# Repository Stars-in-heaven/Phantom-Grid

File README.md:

# PHANTOM GRID

> *Offline-first. Air-gapped. Encrypted. Built for the field.*

Phantom Grid is a series of purpose-built handheld devices engineered for those who operate outside the comfort of connectivity. No Wi-Fi. No cloud sync. No IP assignment. Every hardware and firmware decision is governed by a single principle: **security first, convenience never.**

https://phantom-grid.netlify.app - our site :0 **( has some issues/WIP cuz I keep running out of Netlify credit )**

---

## Series

| ID | Name | Description |
|----|------|-------------|
| **S** | Survival | Bare minimum. Maximum efficiency. Built to run when nothing else does. |
| **T** | Tactical | Feature-packed, encrypted, hardened. Heavy-duty field use. |
| **X** | Experimental | Highly specialised. Each unit unique. Not for general deployment. |
| **C** | Cyber | Fully off-grid. Offensive posture. Maximum resource load. |

---

## Current Build — T-V.1

The first Tactical series device. Dual-panel, hinged form factor with three independent displays, local sensor data, GPS, and an air-gapped file archive terminal.

### Architecture

- **Dual ESP32-C6 SuperMini** — one per side, connected via 4-wire UART hinge link
- **Left side** — Tactical Overwatch Panel (OLEDs, 5-way nav, GPS, moisture, battery)
- **Right side** — Archive Command Terminal (ILI9341 TFT, microSD, tactile buttons)
- **Power** — LiPo 2000–2500mAh → TP4056 (dual protection) → 3.3V buck converter → shared rail via hinge

### Displays

| Display | Role | Interface |
|---------|------|-----------|
| 0.91" OLED 128×32 | Battery, time, date | I²C |
| 1.5" OLED 128×128 | GPS, moisture, sensor data | I²C via TCA9548A |
| 2.4" TFT ILI9341 | File browser, archive terminal | SPI |

### Storage

Files are loaded onto the microSD card by **physically removing it**, writing via USB adapter on a separate machine, and reinserting. No cloud sync. No Wi-Fi. No detectable radio signature. By design.

---

## Build Phases

- [x] **Phase 1** — Architecture & Pinout
- [x] **Phase 2** — Breadboard Prototype
- [ ] **Phase 3** — Firmware Foundation
- [x] **Phase 4** — Feature Layer
- [ ] **Phase 5** — Firmware Hardening
- [ ] **Phase 6** — Physical Build

 (working on getting the components to build the first
  prototype to begin firmware)

---

## Firmware Protection (Phase 5)

- Strip all debug symbols, aggressive optimisation (`-O2/-O3`)
- Obfuscator-LLVM control flow mangling
- CRC/hash self-check on boot — halts if tampered
- Chip ID binding — binds to first chip it runs on, cloning breaks it
- Sensitive logic derived at runtime, never stored plainly in binary
- Binary-only distribution with checksum and signature

---

## Repository Structure

```
phantom-grid/
├── Enclosure/               # Case 3d model
│   ├── Enclosure.f3d
│   ├── Enclosure.step
│   └── Enclosure.stl
|
├── PCBs/               # Kicad PCB files
│   ├── left side/
|   |    ├── left_side.kicad_pcb
|   |    ├── left_side.kicad_pro
|   |    └── left_side.kicad_sch
|   |
│   └── right side/
|       ├── right.kicad_pcb
|       ├── right.kicad_pro
|       └── right.kicad_sch
|  
├── .gitignore
├── README.md    
└── LICENSE

```

---

## Estimated Build Cost

**~£43–80** depending on component sourcing. All parts sourced from AliExpress. Full BOM available in `site/bom.html`.

---

## Progress --  T-V.1

### Left side ( Tactical over-watch Panel )
| Schematic        | PCB           | 3d-view  |
| ------------- |:-------------:| -----:|
|               |  |         |

### Right side ( Archive Terminal Panel )
| Schematic        | PCB           | 3d-view  |
| ------------- |:-------------:| -----:|
|  |  |  |

### ENCLOSURE:
 (It is split in half, but due to this being a prototype it has no screw holes, As I plan to drill them in for testing sizes and such. And then in more final models it will advance to having screw holes.)

---

## Licensing

This project uses a dual licensing model:

| What | Licence | Details |
|------|---------|---------|
| PCB files, enclosure, skeleton firmware | **CERN-OHL-S v2** | Open hardware — modifications must be released under the same licence |
| Full feature firmware | **Proprietary** | Never released — binary only, chip-bound, encrypted |

The open skeleton gives you everything you need to understand how the device is wired and structured. The full firmware with all features ships only with commercially built units and is protected by hardware-level encryption and chip binding. You are free to build your own version using the open source materials — you cannot take the commercial firmware.

---

*PG-T-V.1 / REV.002 / ENCRYPTED / AIR-GAPPED*

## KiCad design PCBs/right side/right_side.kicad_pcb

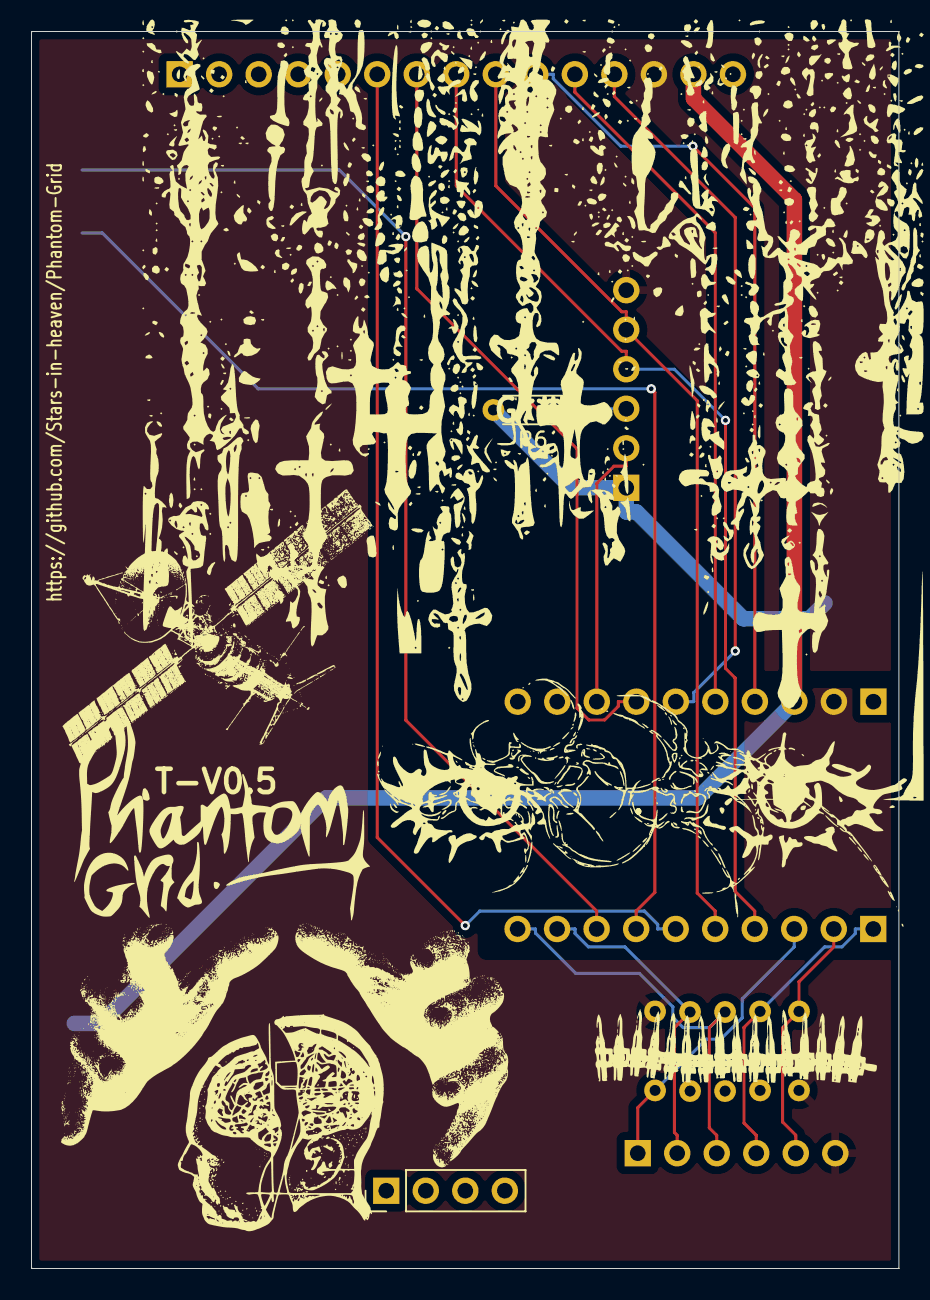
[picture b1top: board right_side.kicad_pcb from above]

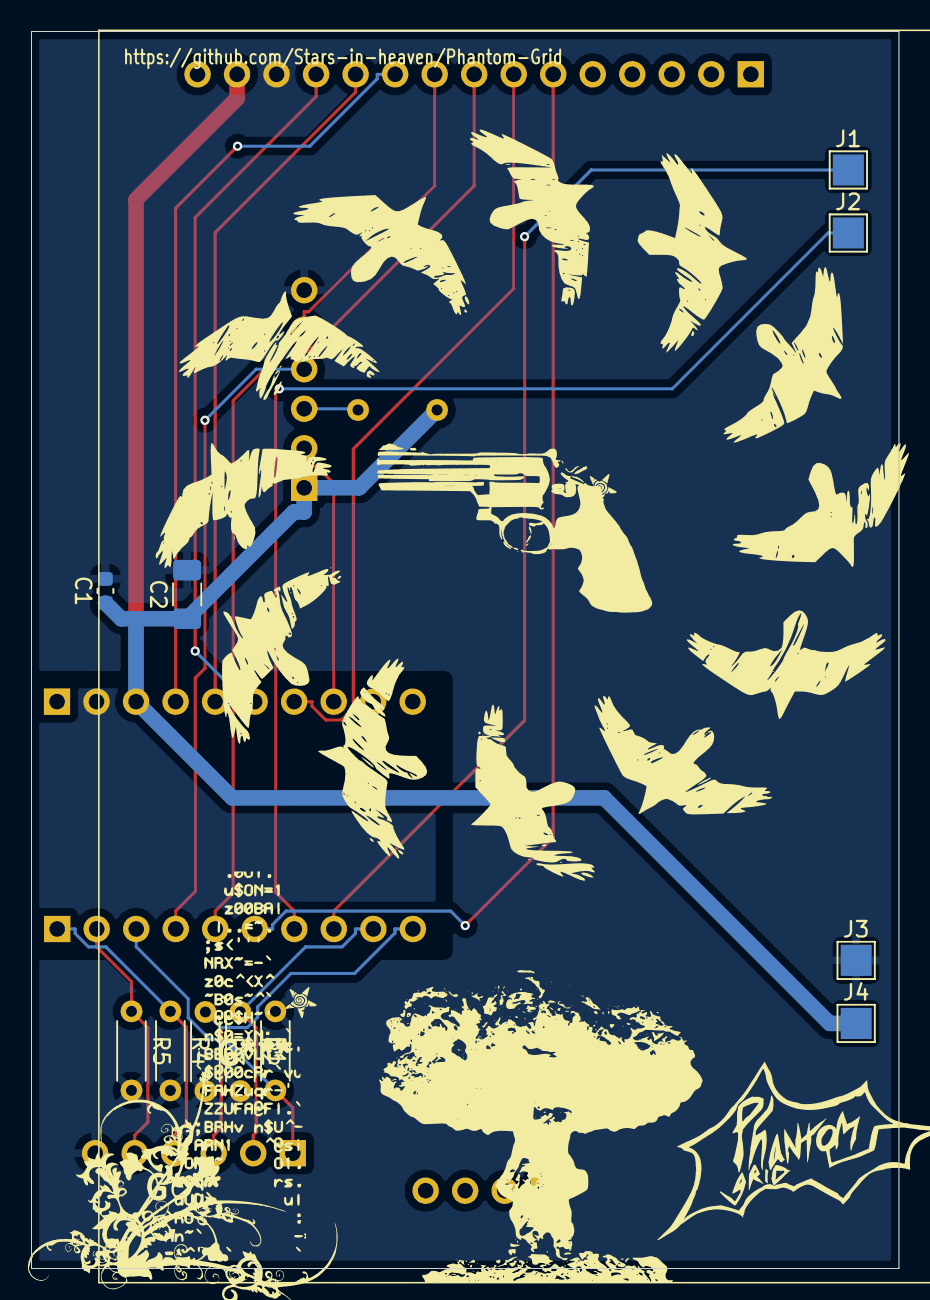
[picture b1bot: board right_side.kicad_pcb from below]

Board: 2 copper layers, 55.8 x 79.5 mm, 18 parts (13 on the bottom side), 18 nets.

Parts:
5-way_nav1: 5 way
.: LOGO
C1: 100nF; C_0603_1608Metric
C2: 10uF; C_1206_3216Metric_Pad1.33x1.80mm_HandSolder
J1: TX HINGE; TestPoint_Pad_2.0x2.0mm
J2: RX HINGE; TestPoint_Pad_2.0x2.0mm
J3: GND HINGE; TestPoint_Pad_2.0x2.0mm
J4: 3V3 HINGE; TestPoint_Pad_2.0x2.0mm
J5: TFT screen; PinHeader_1x15_P2.54mm_Vertical
J7: SD READER; PinHeader_1x06_P2.54mm_Vertical
R1, R2, R3, R4, R5: 10k; R_Axial_DIN0204_L3.6mm_D1.6mm_P5.08mm_Horizontal
R6: 10K; R_Axial_DIN0204_L3.6mm_D1.6mm_P5.08mm_Horizontal
U1: ESP32-C6 MINI
logo 2: LOGO

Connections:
+3V3: C1.1, C2.1, J4.1, J5.14, J7.1, R6.2, U1.13 (3V3)
/HINGE_RX: J2.1, U1.7 (GPIO_04)
/HINGE_TX: J1.1, U1.8 (GPIO_05)
GND: 5-way_nav1.6 (gnd), C1.2, C2.2, J3.1, J5.13, J7.6, R1.2, R2.2, R3.2, R4.2, R5.2, U1.12 (GND)
SD_CS: J7.2, U1.18 (GPIO_10)
SD_MISO: J7.3, R6.1
TFT_CLK: J5.8, J7.4, U1.4 (GPIO_01)
TFT_CS: J5.12, U1.16 (GPIO_21)
TFT_DC: J5.10, U1.14 (GPIO_19)
TFT_LED: J5.7, U1.17 (GPIO_22)
TFT_MISO: J5.6, U1.6 (GPIO_03)
TFT_MOSI: J5.9, J7.5, U1.5 (GPIO_02)
TFT_RST: J5.11, U1.15 (GPIO_20)
back_1: 5-way_nav1.2 (back), R2.1, U1.9 (GPIO_06)
forward_1: 5-way_nav1.1 (forward), R1.1, U1.3 (GPIO_00)
left_1: 5-way_nav1.3 (left), R3.1, U1.10 (GPIO_07)
middle_1: 5-way_nav1.5 (m), R5.1, U1.2 (RX)
right_1: 5-way_nav1.4 (right), R4.1, U1.1 (TX)

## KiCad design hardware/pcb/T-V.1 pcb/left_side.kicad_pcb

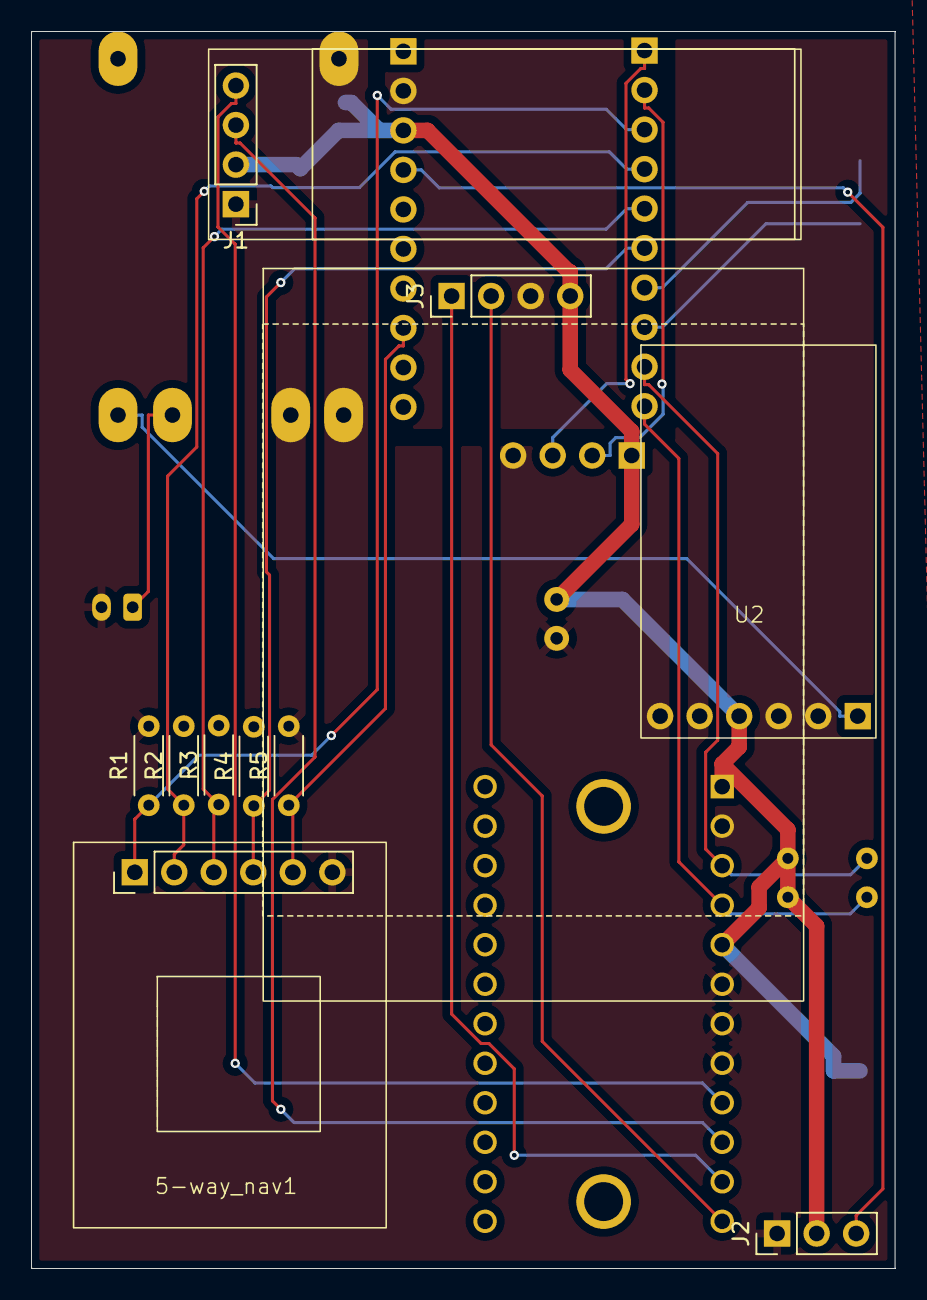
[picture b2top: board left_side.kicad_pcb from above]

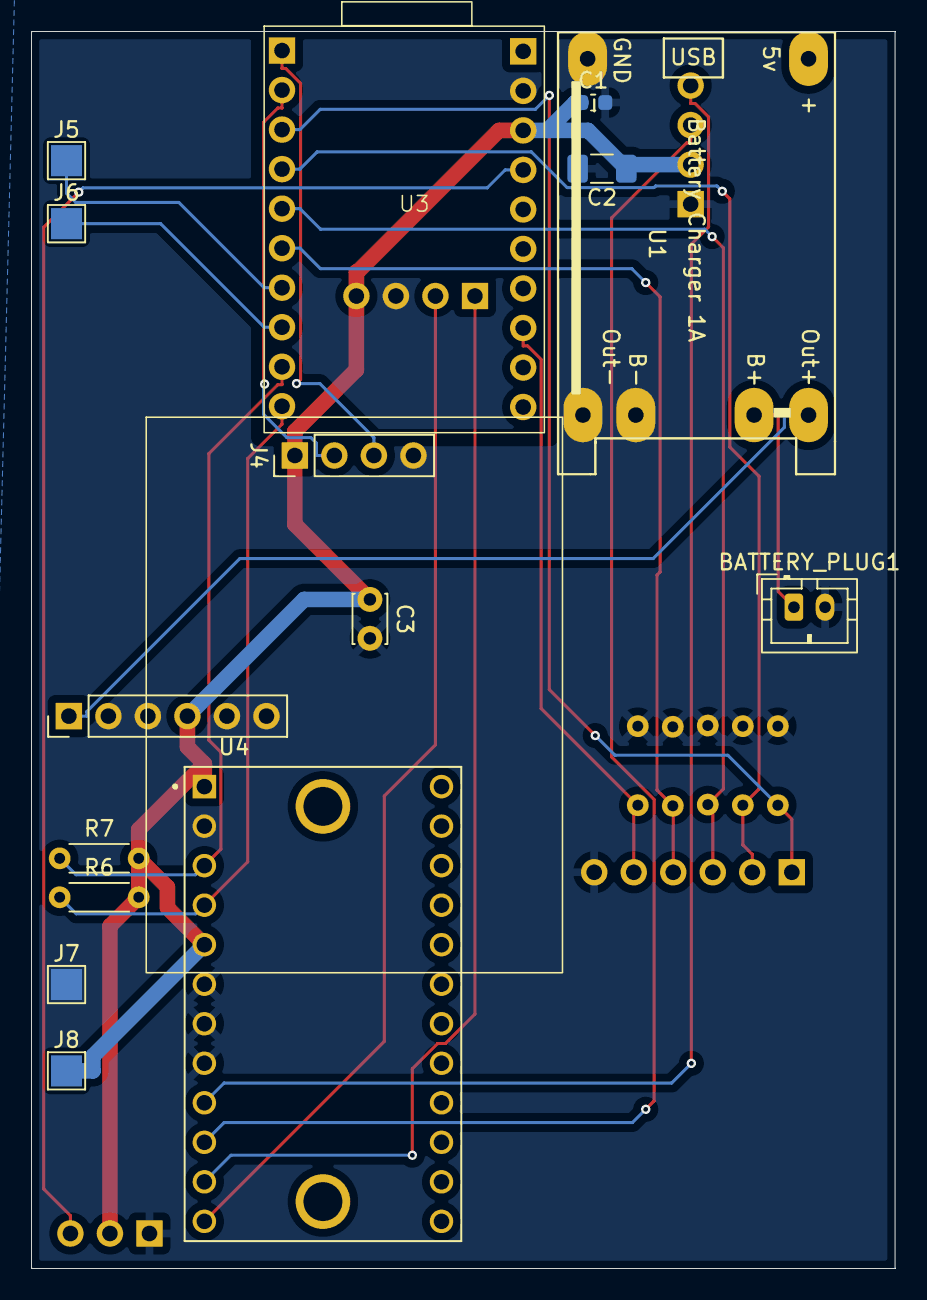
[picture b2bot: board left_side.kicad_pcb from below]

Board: 2 copper layers, 55.5 x 79.5 mm, 24 parts (14 on the bottom side), 20 nets.

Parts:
5-way_nav1: 5 way
BATTERY_PLUG1: B2B-PH-K-S_LF__SN_; JST_PH_B2B-PH-K_1x02_P2.00mm_Vertical
C1: 100nF; C_0603_1608Metric
C2: 10uF; C_1206_3216Metric_Pad1.33x1.80mm_HandSolder
C3: 100nF; C_Disc_D3.0mm_W2.0mm_P2.50mm
J1: MINI oled; PinHeader_1x04_P2.54mm_Vertical
J2: Moisture sensor; PinHeader_1x03_P2.54mm_Vertical
J3: MAIN oled; PinHeader_1x04_P2.54mm_Vertical
J4: GPS; PinHeader_1x04_P2.54mm_Vertical
J5: TX HINGE; TestPoint_Pad_2.0x2.0mm
J6: RX HINGE; TestPoint_Pad_2.0x2.0mm
J7: GND HINGE; TestPoint_Pad_2.0x2.0mm
J8: 3V3 HINGE; TestPoint_Pad_2.0x2.0mm
R1, R2, R3, R4, R5: 10k; R_Axial_DIN0204_L3.6mm_D1.6mm_P5.08mm_Horizontal
R6, R7: 4.7k; R_Axial_DIN0204_L3.6mm_D1.6mm_P5.08mm_Horizontal
U1: tp4056
U2: buck converter
U3: ESP32-C6 MINI
U4: 2717; MODULE_2717

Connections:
+3V3: C1.1, C2.1, C3.1, J1.2, J2.2, J3.4, J4.1, J8.1, R6.2, R7.2, U2.4 (OUT+), U3.13 (3V3), U4.1 (VIN), U4.5 (RST)
/HINGE_RX: J6.1, U3.8 (GPIO_05)
/HINGE_TX: J5.1, U3.7 (GPIO_04)
GND: 5-way_nav1.6 (gnd), BATTERY_PLUG1.2 (B-), C1.2, C2.2, C3.2, J1.1, J2.1, J3.3, J4.4, J7.1, R1.2, R2.2, R3.2, R4.2, R5.2, U1.2 (IN-), U1.4 (B-), U1.6 (O-), U2.2 (IN-), U2.3 (GND), U2.5 (OUT-), U2.6 (GND2), U3.12 (GND), U4.2 (GND), U4.6 (A0), U4.7 (A1), U4.8 (A2)
Moisture sensor: J2.3, U3.14 (GPIO_19)
unnamed: BATTERY_PLUG1.1 (B+), U1.3 (B+)
unnamed: U1.5 (O+), U2.1 (IN+)
RX: J4.2, U3.2 (RX)
SC0: J1.3, U4.10 (SCL0)
SC1: J3.2, U4.12 (SCL1)
SCL: R6.1, U3.10 (GPIO_07), U4.4 (SCL)
SD0: J1.4, U4.9 (SDA0)
SD1: J3.1 (SDA), U4.11 (SDA1)
SDA: R7.1, U3.9 (GPIO_06), U4.3 (SDA)
TX: J4.3, U3.1 (TX)
back: 5-way_nav1.2 (back), R2.1, U3.4 (GPIO_01)
forward: 5-way_nav1.1 (forward), R1.1, U3.3 (GPIO_00)
left: 5-way_nav1.3 (left), R3.1, U3.5 (GPIO_02)
middle: 5-way_nav1.5 (m), R5.1, U3.18 (GPIO_10)
right: 5-way_nav1.4 (right), R4.1, U3.6 (GPIO_03)

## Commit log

2026-03-03 Revise README for Phantom Grid project details
    Expanded the README to provide detailed information about the Phantom Grid project, including device architecture, build phases, firmware protection, repository structure, estimated build cost, and l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
2026-03-03 Add CERN Open Hardware Licence v2
    Added the CERN Open Hardware Licence Version 2 - Strongly Reciprocal to the project.
2026-03-03 Initial commit — add structure, site files, docs and licence
2026-03-03 Add .gitignore — remove .DS_Store
2026-03-04 fixed index
2026-03-04 hopefully fixed html
    issue with link names
2026-03-04 made buttons open in a new tab instead of in the same tab
    cuz im too lazy to add back buttons
2026-03-04 Added Session-summary for phase 1
2026-03-04 Add link to Phantom Grid website
    Added a link to the Phantom Grid website in the README.
2026-03-04 Fix website link format in README
    Updated the link format for the project website in the README.
2026-03-26 Check off completed build phases in README
    Updated build phases to reflect completed tasks.
2026-03-26 Update Phase 6 status to incomplete
2026-03-26 added docs page
2026-03-26 Add Thumbs.db and desktop.ini to .gitignore
2026-03-26 Update Phantom-Grid
2026-03-26 Your commit message
2026-03-26 Revise README with sensor data and progress details
    Updated sensor data description and added progress section.
2026-03-26 Fix formatting of Tactical over-watch Panel section
2026-03-26 Update README with new section for Archive Terminal Panel
2026-03-26 Update images in README for Archive Terminal Panel
2026-03-26 Update README to include enclosure section
    Added enclosure section with an image to the README.
2026-03-26 Clarify website status in README
    Updated website link to indicate it is a work in progress.
2026-03-26 Update README to emphasize site issues
2026-03-26 Update website note in README
    Clarified note about website issues due to Netlify credit.
2026-03-26 Updating PCB files :P
2026-03-26 removing .DS_Stores
    git ignore u lying bitch
2026-03-26 removing .DS_Store
2026-03-26 Update enclosure image and prototype details
    Updated the enclosure image and added a note about screw holes in the prototype.
2026-03-26 Add enclosure files
2026-04-05 Updated structure
2026-04-05 Revise README for accuracy and clarity
    Updated the README to reflect changes in the Tactical Overwatch Panel description, build phases, and repository structure.
